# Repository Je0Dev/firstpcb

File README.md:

>For my first design i followed a playlist from this guy, so check him out: https://www.youtube.com/@HTMWorkshop

---

### First

---

### Second

---

---

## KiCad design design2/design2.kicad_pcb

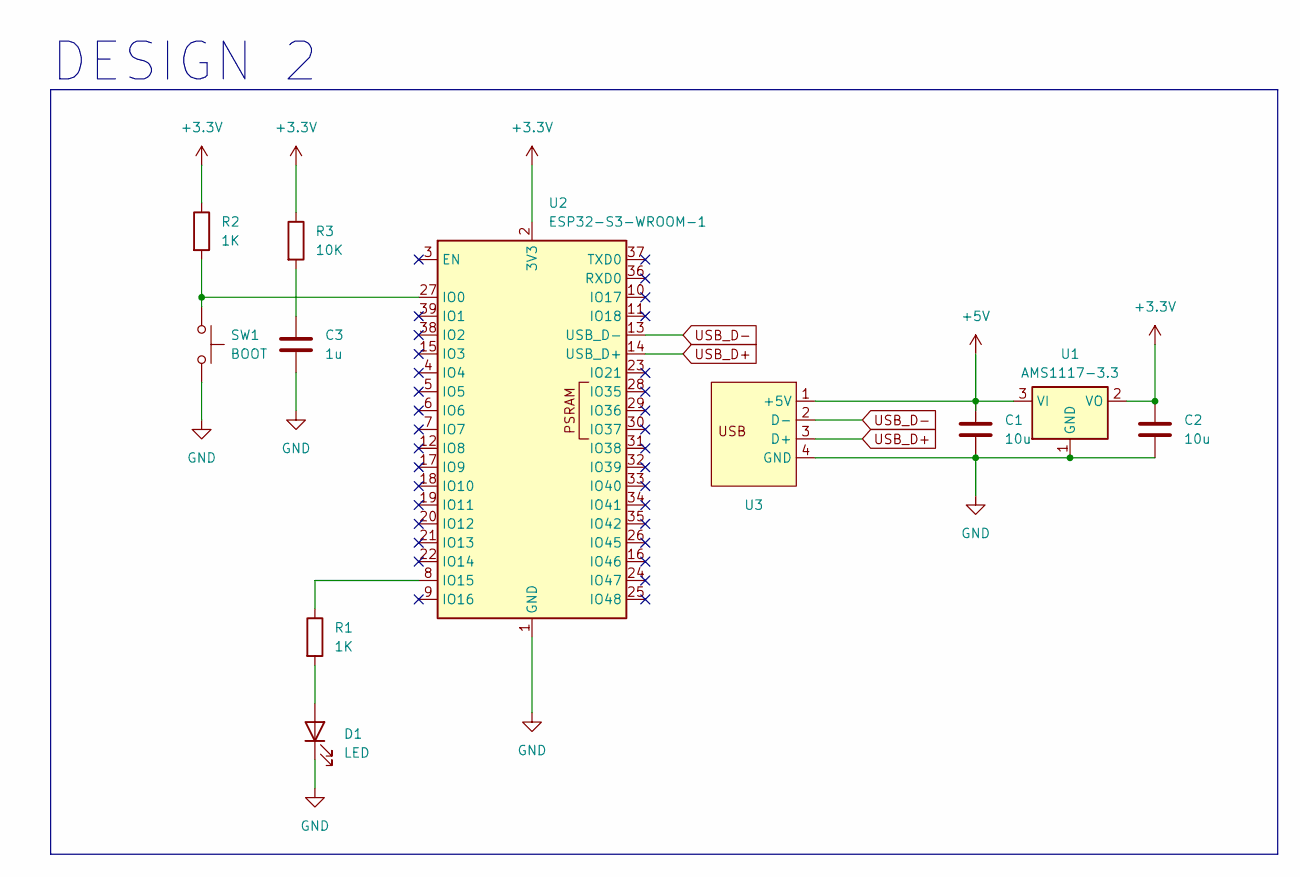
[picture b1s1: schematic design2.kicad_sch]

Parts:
C1, C2: 10u; C_0805_2012Metric_Pad1.18x1.45mm_HandSolder
C3: 1u; C_0805_2012Metric_Pad1.18x1.45mm_HandSolder
D1: LED; LED_0805_2012Metric_Pad1.15x1.40mm_HandSolder
R1, R2: 1K; R_0805_2012Metric_Pad1.20x1.40mm_HandSolder
R3: 10K; R_0805_2012Metric_Pad1.20x1.40mm_HandSolder
SW1: BOOT; SW_Tactile_SPST_NO_Straight_CK_PTS636Sx25SMTRLFS
U1: AMS1117-3.3; SOT-223-3_TabPin2
U2: ESP32-S3-WROOM-1
U3: usb_pcb_connect

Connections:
+3.3V: C2.1, R2.1, R3.1, U1.2 (VO), U2.2 (3V3)
+5V: C1.1, U1.3 (VI), U3.1 (+5V)
GND: C1.2, C2.2, C3.2, D1.1 (K), SW1.2, U1.1 (GND), U2.1 (GND), U2.40 (GND), U2.41 (GND), U3.4 (GND)
unnamed: C3.1, R3.2
unnamed: D1.2 (A), R1.2
unnamed: R2.2, SW1.1, U2.27 (IO0)
unnamed: R1.1, U2.8 (IO15)
USB_D+: U2.14 (USB_D+), U3.3 (D+)
USB_D-: U2.13 (USB_D-), U3.2 (D-)

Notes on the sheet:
DESIGN 2

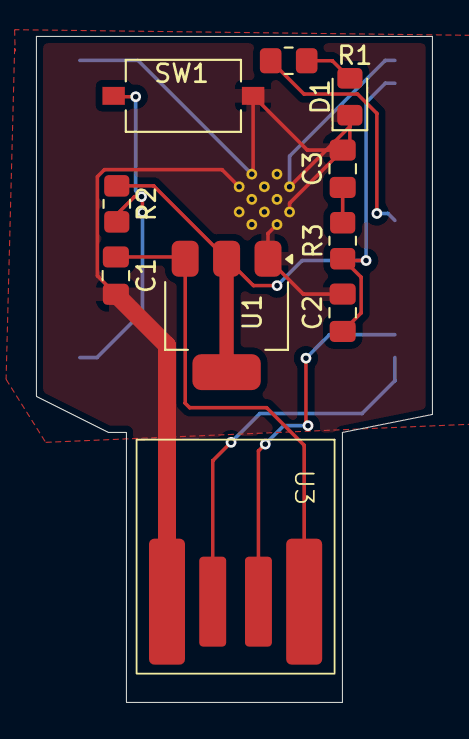
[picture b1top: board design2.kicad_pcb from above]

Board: 2 copper layers, 22.0 x 37.0 mm, 11 parts (1 on the bottom side), 9 nets.

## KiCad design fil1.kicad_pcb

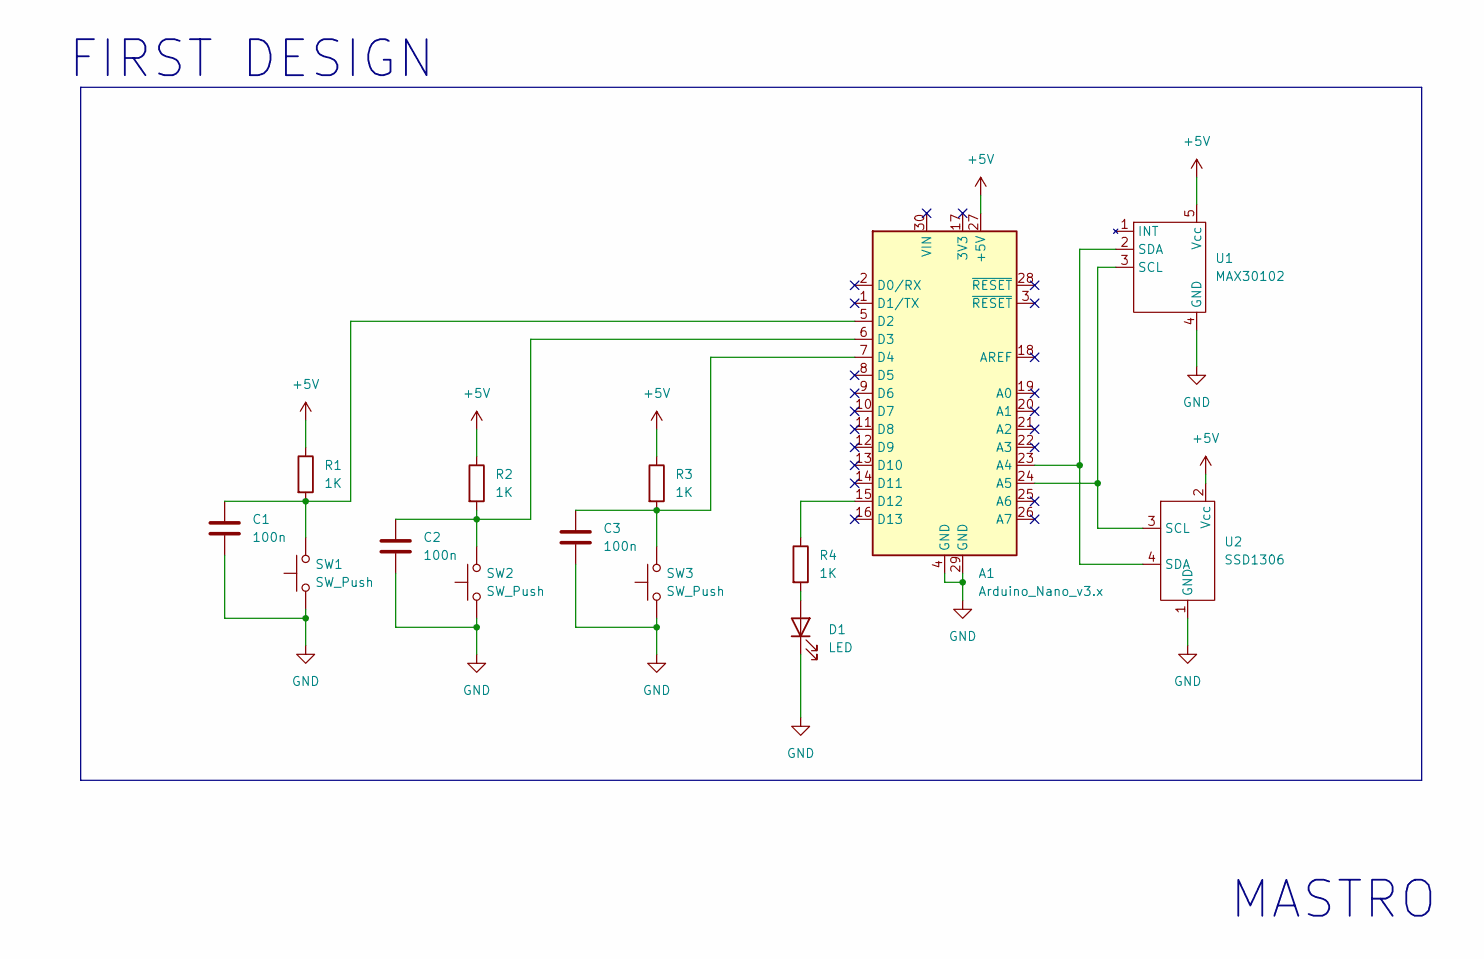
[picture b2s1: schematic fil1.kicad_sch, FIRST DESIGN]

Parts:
A1: Arduino_Nano_v3.x; Arduino_Nano
C1, C2, C3: 100n; C_Disc_D4.7mm_W2.5mm_P5.00mm
D1: LED; LED_D5.0mm
R1, R2, R3, R4: 1K; R_Axial_DIN0207_L6.3mm_D2.5mm_P7.62mm_Horizontal
SW1, SW2, SW3: SW_Push; SW_PUSH_6mm
U1: MAX30102; MAX30102_MODULE
U2: SSD1306

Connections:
+5V: A1.27 (+5V), R1.1, R2.1, R3.1, U1.5 (Vcc), U2.2 (Vcc)
GND: A1.4 (GND), A1.29 (GND), C1.2, C2.2, C3.2, D1.1 (K), SW1.1, SW2.1, SW3.1, U1.4 (GND), U2.1 (GND)
unnamed: A1.23 (A4), U1.2 (SDA), U2.4 (SDA)
unnamed: A1.24 (A5), U1.3 (SCL), U2.3 (SCL)
unnamed: A1.5 (D2), C1.1, R1.2, SW1.2
unnamed: A1.6 (D3), C2.1, R2.2, SW2.2
unnamed: A1.7 (D4), C3.1, R3.2, SW3.2
unnamed: A1.15 (D12), R4.1
unnamed: D1.2 (A), R4.2

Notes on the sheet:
FIRST DESIGN
MASTRO

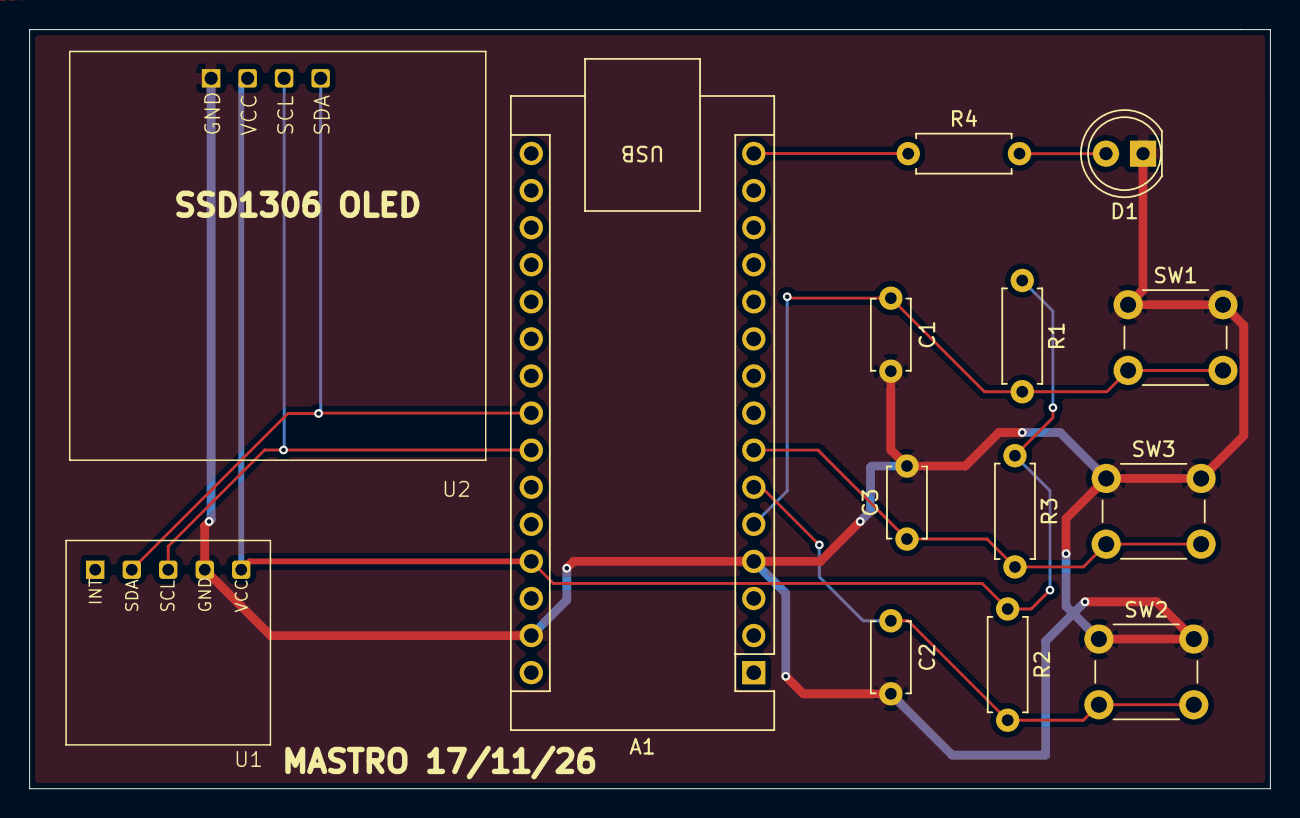
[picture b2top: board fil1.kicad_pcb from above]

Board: 4 copper layers, 85.0 x 52.0 mm, 14 parts (0 on the bottom side), 9 nets.
